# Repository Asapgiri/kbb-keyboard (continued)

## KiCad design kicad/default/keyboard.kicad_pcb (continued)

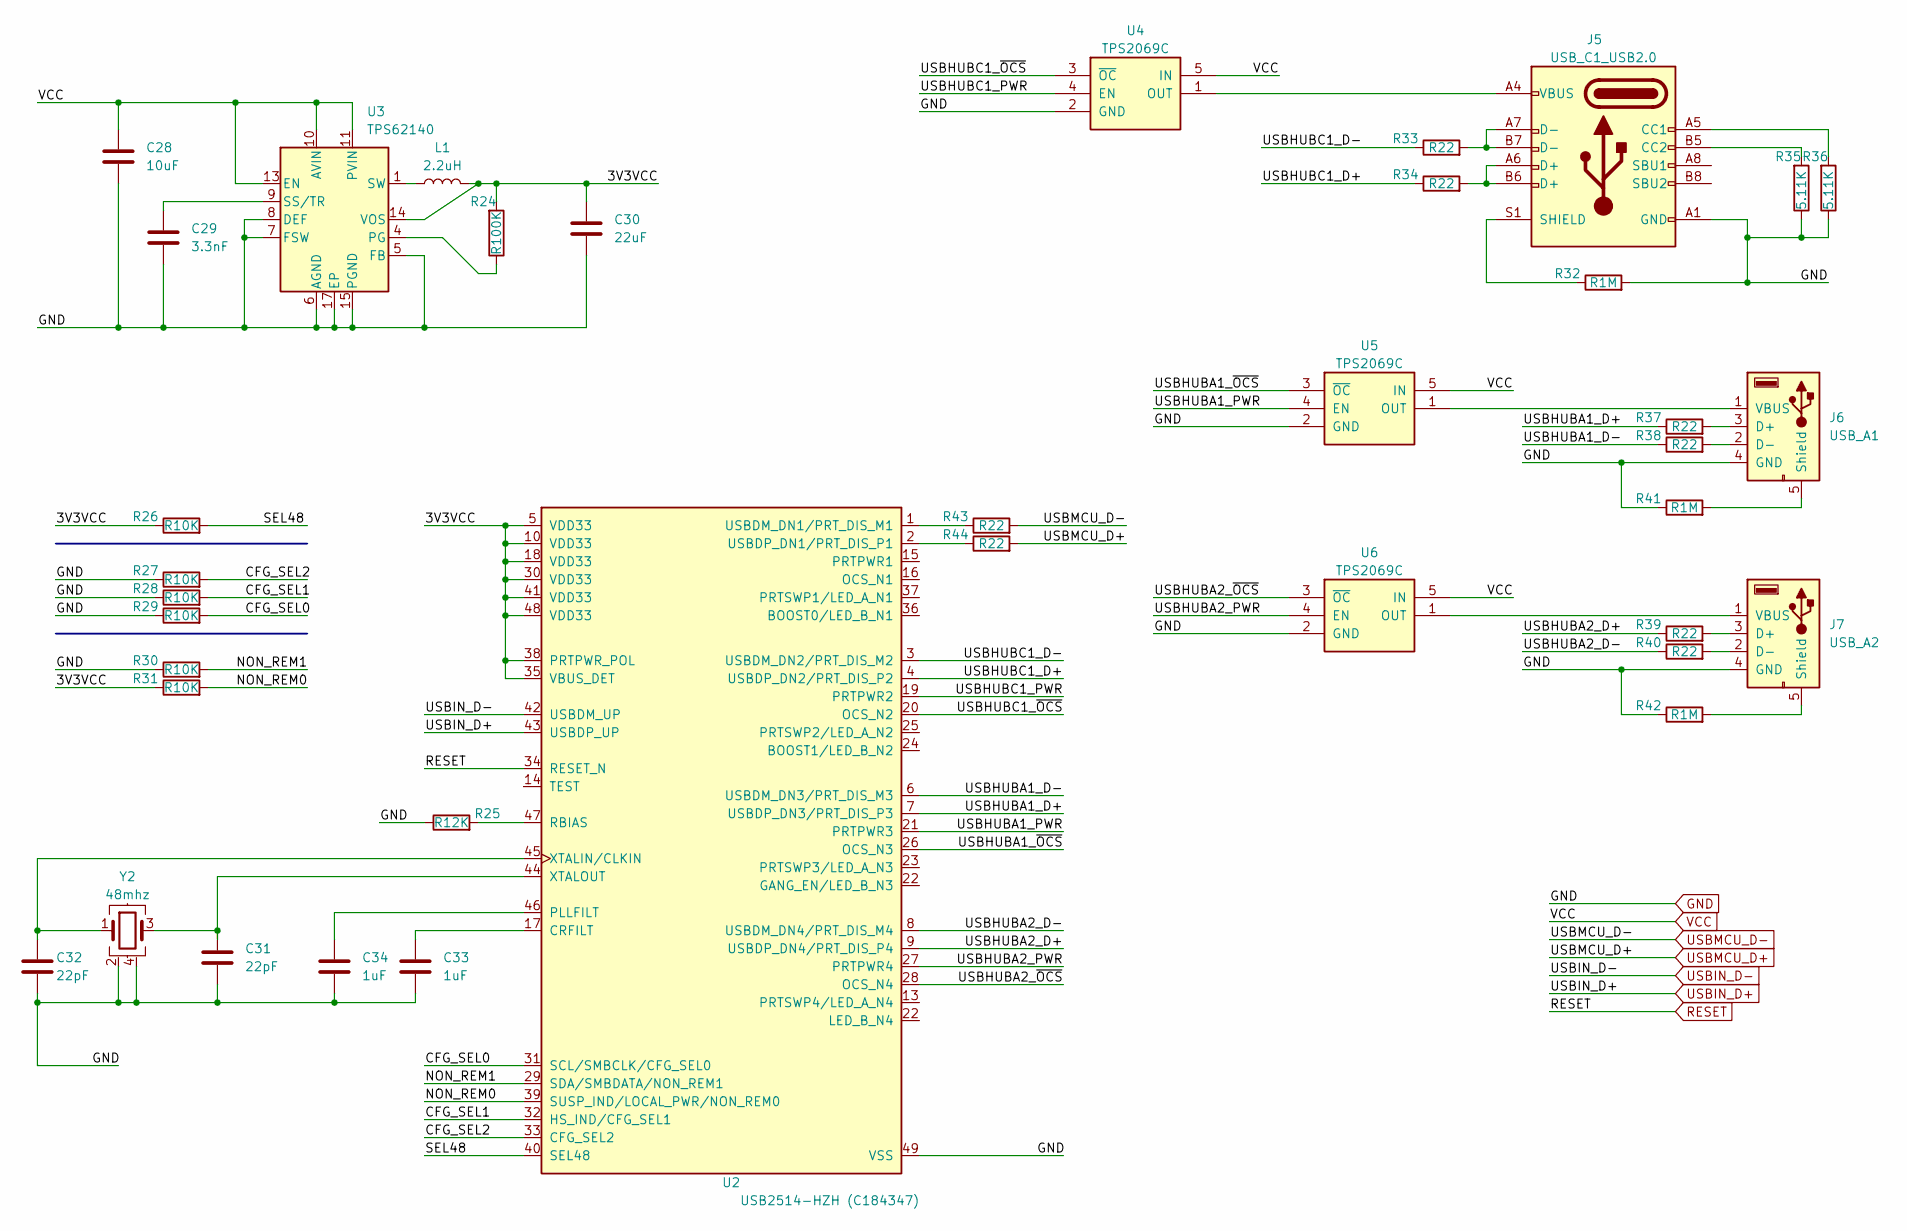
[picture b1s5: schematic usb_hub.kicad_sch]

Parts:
C28: 10uF; C_0402_1005Metric
C29: 3.3nF; C_0402_1005Metric
C30: 22uF; C_0402_1005Metric
C31, C32: 22pF; C_0402_1005Metric
C33, C34: 1uF; C_0402_1005Metric
J5: USB_C1_USB2.0; USB_C_Receptacle_G-Switch_GT-USB-7010ASV
J6: USB_A1; GT_USBA
J7: USB_A2; GT_USBA
L1: 2.2uH; L_0805_2012Metric
R24: R100K; R_0402_1005Metric
R25: R12K; R_0402_1005Metric
R26, R27, R28, R29, R30, R31: R10K; R_0402_1005Metric
R32, R41, R42: R1M; R_0603_1608Metric
R33, R34, R37, R38, R39, R40, R43, R44: R22; R_0402_1005Metric
R35, R36: 5.11K; R_0402_1005Metric
U2: USB2514-HZH (C184347); VQFN-48-1EP_7x7mm_P0.5mm_EP4.1x4.1mm_ThermalVias
U3: TPS62140; VQFN-16-1EP_3x3mm_P0.5mm_EP1.68x1.68mm_ThermalVias
U4, U5, U6: TPS2069C; SOT-23-5
Y2: 48mhz; Crystal_SMD_TXC_7M-4Pin_3.2x2.5mm

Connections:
/USB hub/3V3VCC: C30.1, L1.2, R24.1, R26.1, R31.1, U2.5 (VDD33), U2.10 (VDD33), U2.18 (VDD33), U2.30 (VDD33), U2.35 (VBUS_DET), U2.38 (PRTPWR_POL), U2.41 (VDD33), U2.48 (VDD33), U3.14 (VOS)
/USB hub/CFG_SEL0: R29.2, U2.31 (SCL/SMBCLK/CFG_SEL0)
/USB hub/CFG_SEL1: R28.2, U2.32 (HS_IND/CFG_SEL1)
/USB hub/CFG_SEL2: R27.2, U2.33 (CFG_SEL2)
/USB hub/NON_REM0: R31.2, U2.39 (SUSP_IND/LOCAL_PWR/NON_REM0)
/USB hub/NON_REM1: R30.2, U2.29 (SDA/SMBDATA/NON_REM1)
/USB hub/SEL48: R26.2, U2.40 (SEL48)
/USB hub/USBHUBA1_D+: R37.1, U2.7 (USBDP_DN3/PRT_DIS_P3)
/USB hub/USBHUBA1_D-: R38.1, U2.6 (USBDM_DN3/PRT_DIS_M3)
/USB hub/USBHUBA1_PWR: U2.21 (PRTPWR3), U5.4 (EN)
/USB hub/USBHUBA1_~OCS: U2.26 (OCS_N3), U5.3 (~OC)
/USB hub/USBHUBA2_D+: R39.1, U2.9 (USBDP_DN4/PRT_DIS_P4)
/USB hub/USBHUBA2_D-: R40.1, U2.8 (USBDM_DN4/PRT_DIS_M4)
/USB hub/USBHUBA2_PWR: U2.27 (PRTPWR4), U6.4 (EN)
/USB hub/USBHUBA2_~OCS: U2.28 (OCS_N4), U6.3 (~OC)
/USB hub/USBHUBC1_D+: R34.1, U2.4 (USBDP_DN2/PRT_DIS_P2)
/USB hub/USBHUBC1_D-: R33.1, U2.3 (USBDM_DN2/PRT_DIS_M2)
/USB hub/USBHUBC1_PWR: U2.19 (PRTPWR2), U4.4 (EN)
/USB hub/USBHUBC1_~OCS: U2.20 (OCS_N2), U4.3 (~OC)
GND: C28.2, C29.2, C30.2, C31.2, C32.2, C33.2, C34.2, J5.A1 (GND), J5.A12 (GND), J5.B1 (GND), J5.B12 (GND), J6.4 (GND), J7.4 (GND), R25.1, R27.1, R28.1, R29.1, R30.1, R32.2, R35.2, R36.2, R41.1, R42.1, U2.49 (VSS), U3.5 (FB), U3.6 (AGND), U3.7 (FSW), U3.8 (DEF), U3.15 (PGND), U3.16 (PGND), U3.17 (EP), U4.2 (GND), U5.2 (GND), U6.2 (GND), Y2.2, Y2.4; also elsewhere on the board
unnamed: J5.A5 (CC1), R36.1
unnamed: J5.B5 (CC2), R35.1
unnamed: J5.A6 (D+), J5.B6 (D+), R34.2
unnamed: J5.A7 (D-), J5.B7 (D-), R33.2
unnamed: J5.S1 (SHIELD), R32.1
unnamed: J6.3 (D+), R37.2
unnamed: J6.2 (D-), R38.2
unnamed: J6.5 (Shield), R41.2
unnamed: J6.1 (VBUS), U5.1 (OUT)
unnamed: J7.3 (D+), R39.2
unnamed: J7.2 (D-), R40.2
unnamed: J7.5 (Shield), R42.2
unnamed: J7.1 (VBUS), U6.1 (OUT)
unnamed: L1.1, U3.1 (SW), U3.2 (SW), U3.3 (SW)
unnamed: C33.1, U2.17 (CRFILT)
unnamed: C34.1, U2.46 (PLLFILT)
unnamed: R25.2, U2.47 (RBIAS)
unnamed: R43.1, U2.1 (USBDM_DN1/PRT_DIS_M1)
unnamed: R44.1, U2.2 (USBDP_DN1/PRT_DIS_P1)
unnamed: C32.1, U2.45 (XTALIN/CLKIN), Y2.1
unnamed: C31.1, U2.44 (XTALOUT), Y2.3
unnamed: R24.2, U3.4 (PG)
unnamed: C29.1, U3.9 (SS/TR)
unnamed: J5.A4 (VBUS), J5.A9 (VBUS), J5.B4 (VBUS), J5.B9 (VBUS), U4.1 (OUT)
RESET: U2.34 (RESET_N); also elsewhere on the board
USBIN_D+: U2.43 (USBDP_UP); also elsewhere on the board
USBIN_D-: U2.42 (USBDM_UP); also elsewhere on the board
USBMCU_D+: R44.2; also elsewhere on the board
USBMCU_D-: R43.2; also elsewhere on the board
VCC: C28.1, U3.10 (AVIN), U3.11 (PVIN), U3.12 (PVIN), U3.13 (EN), U4.5 (IN), U5.5 (IN), U6.5 (IN); also elsewhere on the board

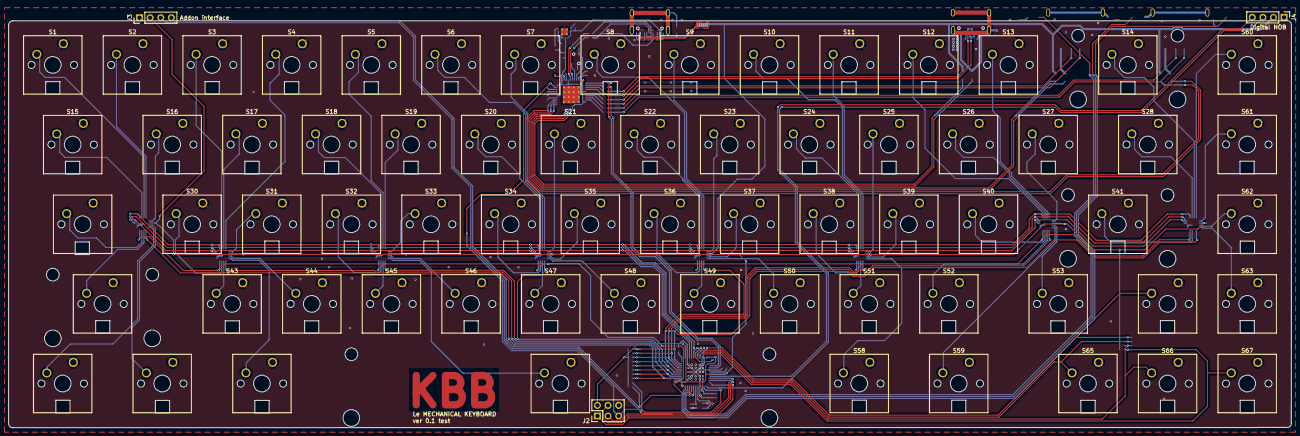
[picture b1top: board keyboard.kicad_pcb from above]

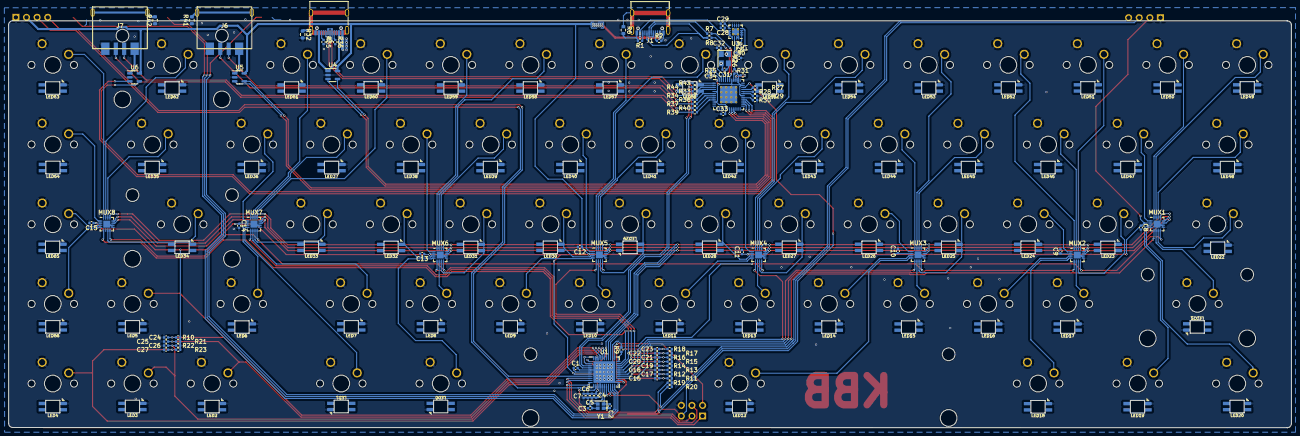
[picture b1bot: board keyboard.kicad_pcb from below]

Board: 2 copper layers, 306.9 x 97.3 mm, 233 parts (163 on the bottom side), 211 nets.

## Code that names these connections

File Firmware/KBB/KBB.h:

#ifndef _KBB_H_
#define _KBB_H_

#include "MapInterface.h"
//#include <HID-Project.h>

#define SEGMENT_DELAY_US    50

#define PIN_BOARD_EN  3

#define PIN_ADDR_A0 7
#define PIN_ADDR_A1 19
#define PIN_ADDR_A2 18

#define PIN_SEG0 4
#define PIN_SEG1 12
#define PIN_SEG2 6
#define PIN_SEG3 8
#define PIN_SEG4 9
#define PIN_SEG5 10
#define PIN_SEG6 5
#define PIN_SEG7 13

#define PIN_ARROW_UP    23
#define PIN_ARROW_DOWN  21
#define PIN_ARROW_LEFT  22
#define PIN_ARROW_RIGHT 20

#define PIN_LED0          30
#define PIN_LED1          1
#define PIN_LED2          0
#define PIN_LED_CAPSLOCK  PIN_LED0
#define PIN_LED_WINLOCK   PIN_LED1
#define PIN_LED_FNLOCK    PIN_LED2


#define NUMBER_OF_ARROWS  4
#define NUMBER_OF_SEGS    8
#define KEYS_IN_SEGS      8

#define KEY_LEFT_SLEEP    NULL  //NULL  // 0x5F
#define KEY_VOLUME_UP     NULL  //MEDIA_VOLUME_UP
#define KEY_VOLUME_DOWN   NULL  //MEDIA_VOLUME_DOWN
#define KEY_MUSIC_PLAY    NULL  //MEDIA_PLAY_PAUSE
#define KEY_MUSIC_NEXT    NULL  //MEDIA_NEXT
#define KEY_MUSIC_PREV    NULL  //MEDIA_PREVIOUS

#define FUNCTION_KEY    0x1

#define KEY_BUFFER_TYPE         unsigned int
#define KEY_BUFFER_SIZE         (sizeof(KEY_BUFFER_TYPE) << 3)  //  * 8
#define KEY_BUFFER_ACCEPT_TRUE  (sizeof(KEY_BUFFER_TYPE) >> 1)  //  / 2
#define KEY_BUFFER_SIZE_FILER   (KEY_BUFFER_SIZE - 1)   // 0b00000111 = 0x07, accept from 0 to 7


struct char_holder {
  unsigned char def;
  unsigned char fn;
  void (*fn_press)(void);
  void (*fn_release)(void);
};

struct key_map {
  KEY_BUFFER_TYPE buffer;
  KEY_BUFFER_TYPE buffer_pos;
  bool actual;
  bool last;
  bool press;
  bool release;
};



class KBB{
private:
  MapInterface* mapInterface;
  void setMaps();
  unsigned int segment;
  bool fn_pressed;

  struct key_map KeyMapMain[NUMBER_OF_SEGS][KEYS_IN_SEGS];
  struct key_map KeyMapArrows[NUMBER_OF_ARROWS];

  void HandleSendChange(struct char_holder* key, bool press);
  inline void SendPress(char key);
  inline void SendRelease(char key);
  bool CompareLastKeys(struct key_map* keymap, unsigned int len);
  char SaveToEEPROM();
  char ReadFromEEPROM();
  char EEPROM_init();

public:
  void begin();
  void ChangeSegment(unsigned int seg);

  void RefreshKeyMap();
  bool CompareLastKeys();
  void SendSegment();
  void SaveToPastSegment();

  void SyncKeyMap();

  KBB();
  KBB(MapInterface* mapInterface);
  ~KBB();
};


#endif // _KBB_H_

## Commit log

2023-07-22 init with keyboard files
2023-07-22 Firmware skeleton
2023-07-22 adawdawd
2023-07-22 added hello world with Keyboard.h
2023-07-22 +Segment changing method
2023-07-22 Segment Checking skeleton
2023-07-22 Pinmode setting for segment inputs
2023-07-22 Some serious shit
2023-07-22 minor changes
2023-07-22 Spacing Enters added
2023-07-22 spacings and read in changes for readability
2023-07-22 restore
2023-07-22 nearly working
2023-07-23 Kinda working thing
2023-07-23 Working demo
2023-07-23 Functioning as a real keyboard.
2023-07-23 2D array merge by hand
2023-07-23 Fix missed merge
2023-07-23 delay reduced
2023-07-23 Advanced mapping with defined keys
2023-07-23 Fn press main logic
2023-07-24 arrow keys initialized
2023-07-24 function keys
2023-07-24 Plus fn keys and fn lock.
2023-07-24 battery connectors with diodes. (Should be replaced to FETs before production)
2023-07-24 Udtate README.md
2023-07-24 Compile error fixes
2023-07-24 Remove unnecessary files and add pullups for arrow keys.
2023-07-24 Arrows present in firmware
2023-07-25 Console Desktop Utility Added
2023-07-25 Changed from c to cpp
2023-07-25 Changed gitignore
2023-07-25 remove generated
2023-07-25 gitignore add
2023-07-25 Add .vscode/c_cpp_properties.json to vscode
2023-07-25 Remove unnecessary files
2023-07-25 KBB Serial lib added
2023-07-25 This branch made for the Desktop App feature
    !!!NOT WORKING!!!
2023-07-25 No feature but working version added
    Working version
2023-07-25 Preversion
2023-07-26 Keyboard extension interface written
2023-07-26 Save layout to EEPROM
2023-07-26 Battery planning
2023-07-26 EEPROM and DesktopMapInterface
2023-07-26 interface renamed
2023-07-26 add board enable
2023-07-26 Added 3.3V
2023-07-27 wireing
2023-07-27 usb hub wireing half
2023-07-27 Map can be updatable from pc.
2023-07-27 Implement USB Hub
2023-07-27 shematic and pcb update
2023-07-29 I commit my case files.
2023-07-31 new versions and finalized wired version
2023-08-02 Added plate design
2023-08-03 Case design for version 0.1
2023-08-03 Cut parts
2023-08-03 foots
2023-08-04 Plate dising and key modifications
2023-08-04 Modify keys to correct locations and remove Serial calls
2023-08-04 Extended fn functions porgression
2023-08-04 Remove unnececcary keys
2023-08-04 led back
2023-08-04 platek
2023-08-08 Function key correction
2023-08-11 Update README.md
    Function keys combination and meaning
2023-08-11 keydefinitions
2023-08-11 Update README.md
    Updated layout
2023-08-11 Update README.md
    Keyboard layout updated
2023-08-11 readme
2023-08-13 New case
2023-08-22 New inventor casings for better patent
2023-08-22 Remove unnececcary
2023-10-11 implementation of debouncing filter for key press
2023-10-18 different appoach for debounce implementation
2023-12-21 Add key filtering for better typing
2024-02-24 Put keyboard project to CMakeLists.txt instead of arduino project
2024-02-24 Rearrange folder structure
2024-02-25 Move toolchain to CLI only
2024-03-11 Add LEDs to PCB
